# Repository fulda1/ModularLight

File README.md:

# ModularLight
Modular Light is project of light modules useful for construction sets loke lego etc.

See description in <A HREF="https://github.com/fulda1/ModularLight/wiki">Wiki</A>

<IMG SRC="https://raw.githubusercontent.com/fulda1/ModularLight/main/images/by-nc-sa.eu.svg">

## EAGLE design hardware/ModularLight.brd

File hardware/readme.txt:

Shematic and printed circuit boards

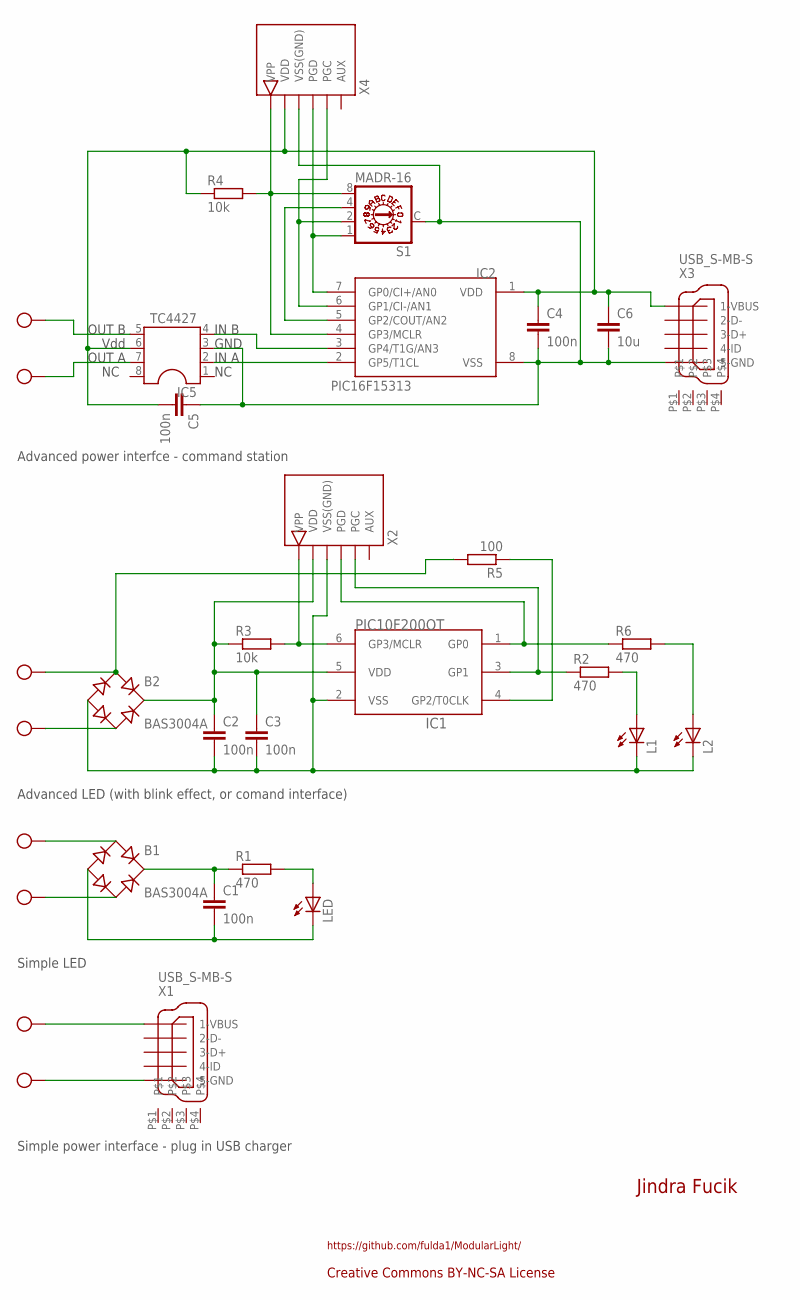
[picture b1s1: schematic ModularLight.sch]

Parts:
B1, B2: BAS3004A; SOT143
C1, C2, C3, C4, C5: 100n; C0805
C6: 10u; C0805
IC1: PIC10F200OT; SOT23-6
IC2: PIC16F15313; SO-08
IC5: TC4427; SO-08
J1, J2, J3, J4: PINHEAD_B; 2PIN_L
L1, L2: LED3MM_I
LED: LED3MM_I
R1, R2, R6: 470; R0805
R3, R4: 10k; R0805
R5: 100; R0805
S1: MADR-16; P103
X1, X3: USB_S-MB-S; USB-MB-S
X2, X4: PICKITXS; 6PIN3

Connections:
unnamed: J1.1, X1.VBUS (1-VBUS)
unnamed: J1.2, X1.GND (5-GND)
unnamed: B1.2 (AC1), J2.1
unnamed: B1.3 (AC2), J2.2
unnamed: B1.1 (-), C1.2, LED.K (C)
unnamed: B1.4 (+), C1.1, R1.1
unnamed: LED.A, R1.2
unnamed: B2.2 (AC1), J3.1, R5.2
unnamed: B2.3 (AC2), J3.2
unnamed: B2.1 (-), C2.2, C3.2, IC1.2 (VSS), L1.K (C), L2.K (C), X2.P$3 (VSS(GND))
unnamed: IC5.7, J4.2
unnamed: L1.A, R2.2
unnamed: IC1.4 (GP2/T0CLK), R5.1
unnamed: IC1.6 (GP3/MCLR), R3.2, X2.P$1 (VPP)
unnamed: B2.4 (+), C2.1, C3.1, IC1.5 (VDD), R3.1, X2.P$2 (VDD)
unnamed: IC1.3 (GP1), R2.1, X2.P$5 (PGC)
unnamed: IC1.1 (GP0), R6.1, X2.P$4 (PGD)
unnamed: IC5.5, J4.1
unnamed: C4.2, C5.1, C6.2, IC2.8 (VSS), IC5.3, S1.C, X3.GND (5-GND), X4.P$3 (VSS(GND))
unnamed: C4.1, C5.2, C6.1, IC2.1 (VDD), IC5.6, R4.1, X3.VBUS (1-VBUS), X4.P$2 (VDD)
unnamed: L2.A, R6.2
unnamed: IC2.2 (GP5/T1CL), IC5.2
unnamed: IC2.3 (GP4/T1G/AN3), IC5.4
unnamed: IC2.7 (GP0/CI+/AN0), S1.1, X4.P$4 (PGD)
unnamed: IC2.6 (GP1/CI-/AN1), S1.2, X4.P$5 (PGC)
unnamed: IC2.5 (GP2/COUT/AN2), S1.4
unnamed: IC2.4 (GP3/MCLR), R4.2, S1.8, X4.P$1 (VPP)

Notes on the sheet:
Simple power interface - plug in USB charger
Simple LED
Advanced LED (with blink effect, or comand interface)
Advanced power interfce - command station
IN A
GND
IN B
OUT B
OUT A
Vdd
Jindra Fucik
Creative Commons BY-NC-SA License
https://github.com/fulda1/ModularLight/

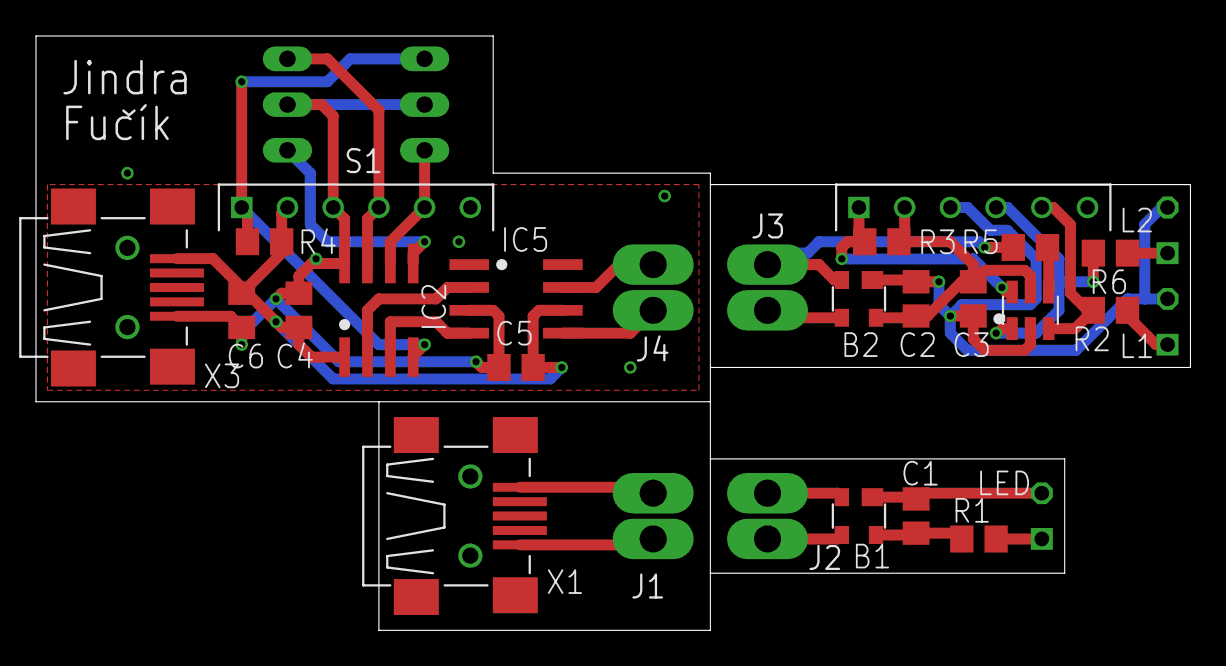
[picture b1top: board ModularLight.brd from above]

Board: 2 copper layers, 64.1 x 33.0 mm, 29 parts (0 on the bottom side), 27 nets.

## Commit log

2022-03-11 Create LICENSE
    Creative Commons BY NC SA
2022-03-11 added schematic and board
2022-03-11 images
2022-03-11 create software folder
2022-03-11 Added source codes
2022-03-11 Update license
2022-03-11 Updated license
2022-03-11 updated description
2022-03-22 add files for wiki
